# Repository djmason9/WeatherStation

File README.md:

## Weather Station Widget
---
This widget will tell you the current weather as well as a 3 day forcast and the phase of the current moon.

## API's
---
It uses the Darksky Free API to gather all its data.

https://darksky.net/

https://api.darksky.net/forecast/[API_KEY]/33.307575,-111.844940?exclude=minutely,hourly,alerts,flags

## Drivers
For the ESP32 you might need to install drivers for the USB
https://www.silabs.com/products/development-tools/software/usb-to-uart-bridge-vcp-drivers

## Libraries
---
I used ArduinoJson lib (5.13.5) to parse the response from the API, the WiFI lib to connect to the WiFi Access Point. 

The https://github.com/ThingPulse/esp8266-oled-ssd1306 is a great LCD lib to allow the ESP32 to chip to easily communitcate with the display

ESP32 chip install
https://dl.espressif.com/dl/package_esp32_index.json

I wrote my own font lib and graphics lib for the graphics using:

http://oleddisplay.squix.ch/#/home for fonts and

http://chilipeppr.com/esp32 to convert the images

Images are in `WeatherGraphics.h` and `MoonPhase.h`

``time.h`` and ``math.h`` are used to format the Unix time stamps to a readable date and round temperatures

```c
#include "WeatherGraphics.h"
#include "CustomDisplayFonts.h"
#include "MoonPhase.h"
#include <ArduinoJson.h>
#include <WiFi.h>
#include <HTTPClient.h>
#include "SSD1306.h"
#include "ArduinoSort.h"
#include "time.h"
#include "math.h"
```

## To Run Update
You will need to update the following items
```
[YOUR SECRET KEY]
[YOUR SSID NETWORK NAME]
[YOUR NETWORK PASSWORD]
```

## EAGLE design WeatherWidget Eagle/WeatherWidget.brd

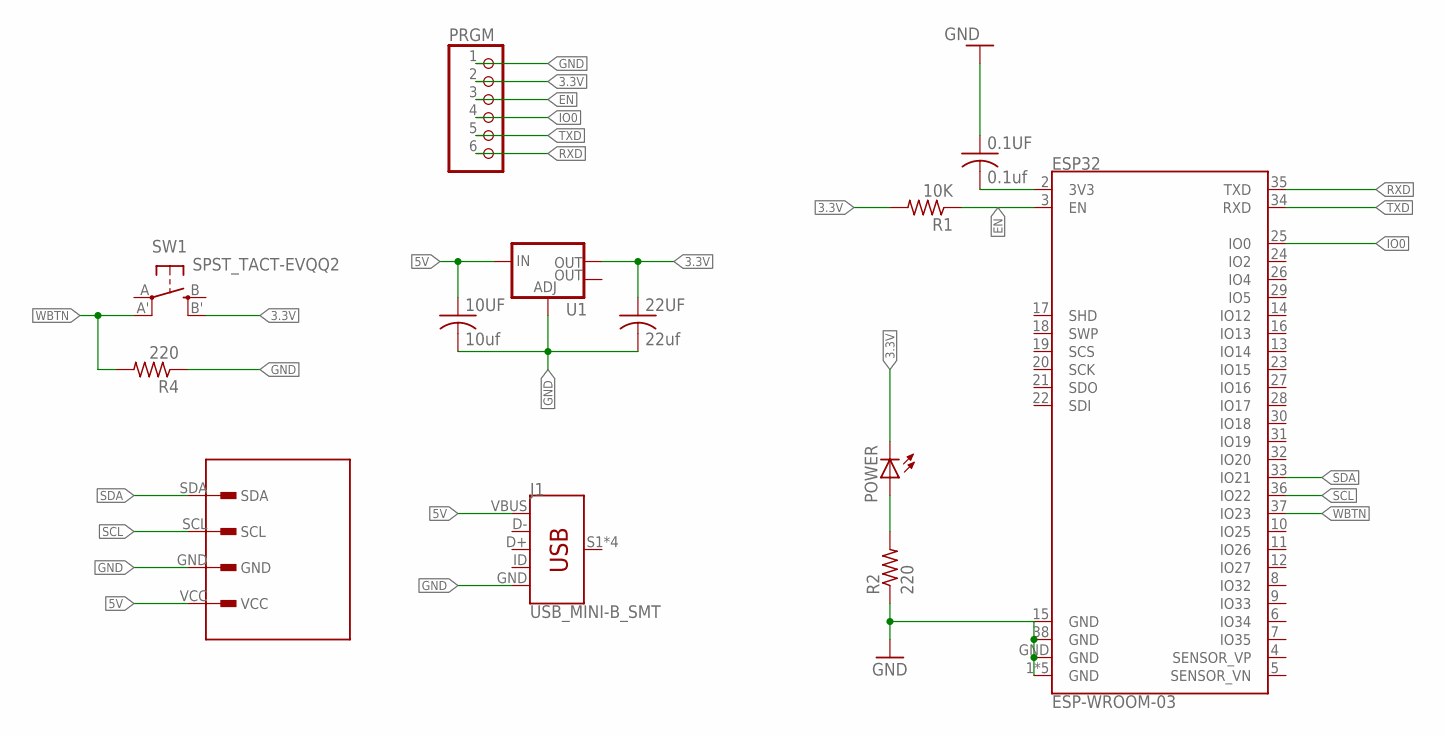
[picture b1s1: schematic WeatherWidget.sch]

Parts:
0.1UF: 0.1uf; C0805K
10UF: 10uf; C0805K
22UF: 22uf; C0805K
128X1: 128X64OLED
ESP32: ESP-WROOM-03; ESP-WROOM-03-HOLES
J1: USB_MINI-B_SMT; USB-MINIB
POWER: LEDCHIP-LED0805; CHIP-LED0805
PRGM: PINHD-1X6; 1X06
R1: 10K; R0805
R2, R4: 220; R0805
SW1: SPST_TACT-EVQQ2; EVQ-Q2
U1: V_REG_LM1117SOT223; SOT223

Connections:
3.3V: 22UF.1, POWER.C, PRGM.2, R1.2, SW1.B' (S1), U1.2 (OUT)
5V: 10UF.1, 128X1.VCC, J1.VBUS, U1.3 (IN)
EN: ESP32.3 (EN), PRGM.3, R1.1
GND: 0.1UF.1, 10UF.2, 22UF.2, 128X1.GND, ESP32.1 (GND), ESP32.15 (GND), ESP32.38 (GND), ESP32.GND, ESP32.GND1 (GND), ESP32.GND2 (GND), ESP32.GND3 (GND), ESP32.GND4 (GND), J1.GND, PRGM.1, R2.1, R4.1, U1.1 (ADJ)
IO0: ESP32.25 (IO0), PRGM.4
unnamed: POWER.A, R2.2
unnamed: 0.1UF.2, ESP32.2 (3V3)
RXD: ESP32.35 (TXD), PRGM.6
SCL: 128X1.SCL, ESP32.36 (IO22)
SDA: 128X1.SDA, ESP32.33 (IO21)
TXD: ESP32.34 (RXD), PRGM.5
WBTN: ESP32.37 (IO23), R4.2, SW1.A' (P1)

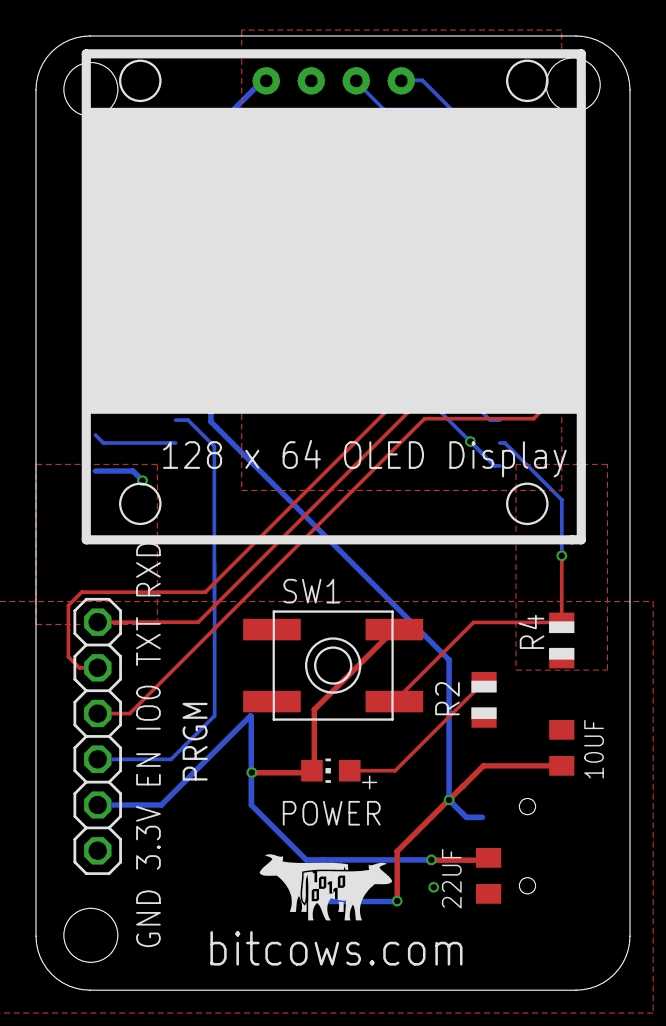
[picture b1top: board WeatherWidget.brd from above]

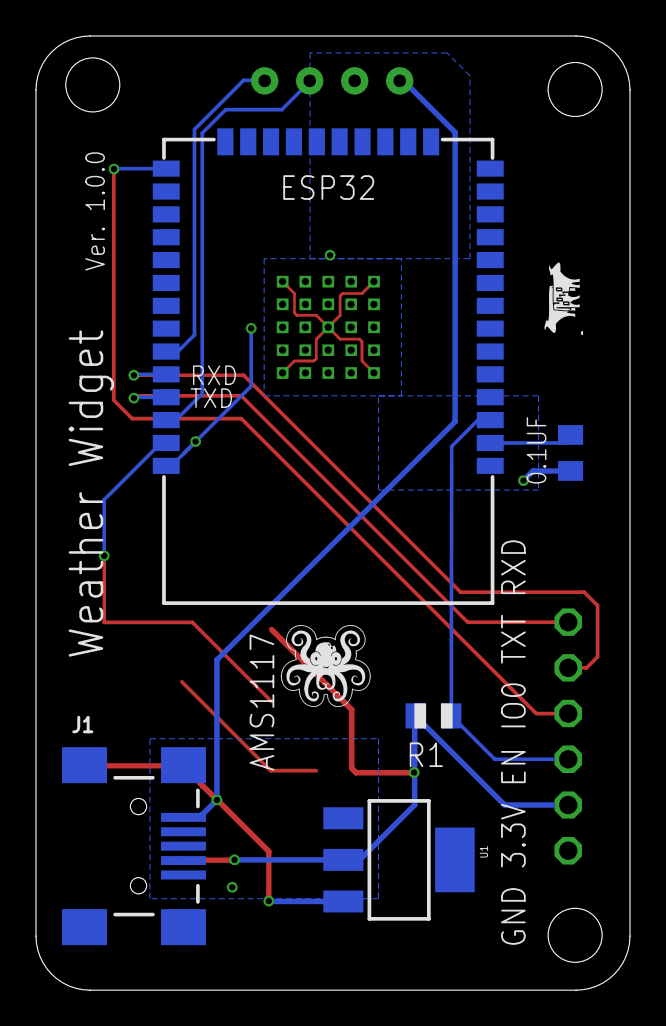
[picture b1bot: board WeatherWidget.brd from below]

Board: 2 copper layers, 33.0 x 53.0 mm, 16 parts (7 on the bottom side), 12 nets.

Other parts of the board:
U$1: BITCOWS_SM
U$2: BITCOWS
U$3: SFE_LUDUS-S

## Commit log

2019-10-10 updated board info
2019-10-16 updated esp32 footprint

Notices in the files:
parts and their libraries:
SparkFun-IC-Power: Licensing: Creative Commons ShareAlike 4.0 International - https://creativecommons.org/licenses/by-sa/4.0
